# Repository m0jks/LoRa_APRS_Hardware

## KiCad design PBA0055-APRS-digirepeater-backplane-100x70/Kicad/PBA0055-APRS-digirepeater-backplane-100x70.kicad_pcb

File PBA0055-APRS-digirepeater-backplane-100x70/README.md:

This project is a Simple carrier board for a Heltec Lora WiFi V3 board.

This board can be purchased from Amazon or Aliexpress:

	https://www.aliexpress.com/item/1005007594267069.html

For LoRa APRS buy the EU433 version, for Meshtastic buy the EU868 version

The Kicad PCB in the "Kicad" directory is designed to fit in the following (120x90x70) IP67 case:

	https://www.aliexpress.com/item/1005005387771681.html

In the "Freecad" directory you will find three 3D design files.They are as follows:

1. LoRa_APRS_node_mounting_plates_100x70_studs.FCStd

This is a mounting place for the Kicad PCB inside the body of the IP67 case. It raises the PCB so that the N-Type to IPEX fitting sits neatly underneath it (and the PCB ground plane).

2. IP67_Case_38mm_mast_clamp.FCStd

This is an external mounting fixture fo the (120x90x70) case - to a 1.5" (38mm) mast. It requires two M4 nuts and bolts to clamp the two halves together.

3. IP67_Case_Antenna_Hole_Template.FCStd

This is a hole drilling template for the top N-Type and bottom SP13 power connector.

Additional Hardware.

In addition to the above PCB and 3D printed files, to complete this design you will need the following parts

1. N-Type to IPEX (U.FL) pigtail

2. SP13 Male and Female Connector

3. LM2596S Buck DC-DC board.

4. JST 1.25mm (2P) SMA

5. EU433 or EU868 Antenna

6. Heltec LoRa V3 WiFi board. EU433 for APRS, EU868 for Meshtastic

The above are all available from Aliexpress of Amazon:

1. https://www.aliexpress.com/item/1005007261632487.html
2. https://www.aliexpress.com/item/1005006769201518.html
3. https://www.aliexpress.com/item/1005006516043406.html
4. https://www.aliexpress.com/item/1005005721470475.html
5  https://www.aliexpress.com/item/1005006253283206.html
6. https://www.aliexpress.com/item/32886711232.html

Finally it is important to remember that LM2596S Buck DC-DC board has a pot top right. You need to make sure you twiddle that until the ouput (right hand side) is 5v. This is because the above PCB supplies the Heltec board with a 5v supply on pin 1

Any questions, get in touch

Dave {https://www.qrz.com/db/M0JKS)

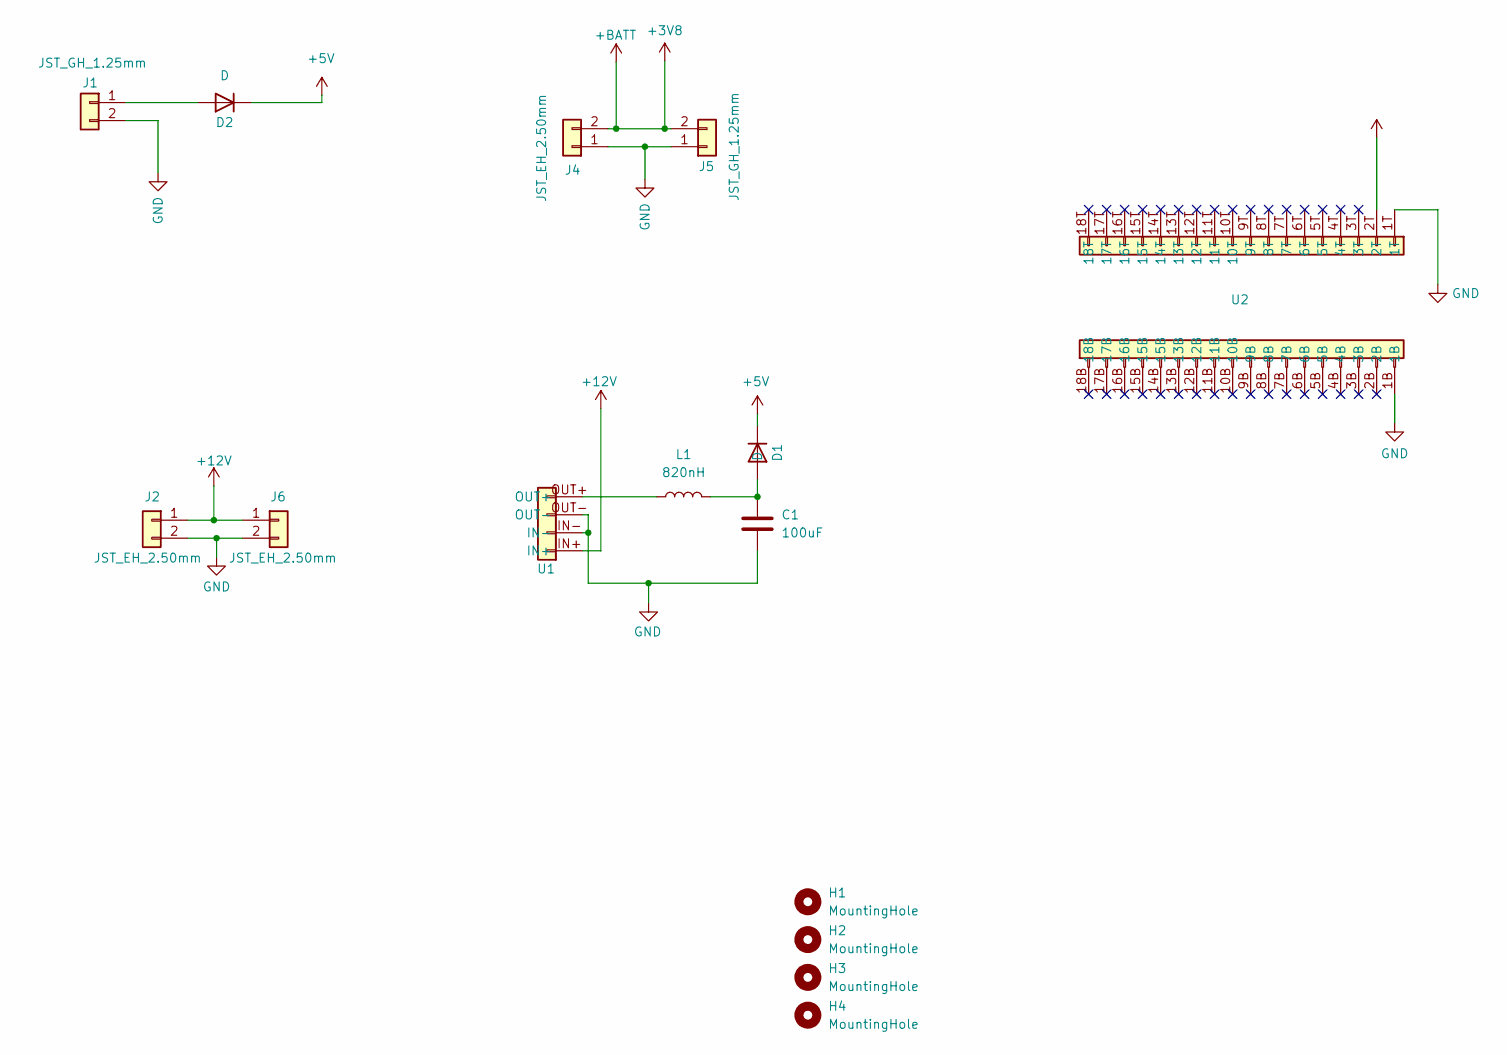
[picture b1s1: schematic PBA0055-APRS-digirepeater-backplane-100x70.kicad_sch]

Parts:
C1: 100uF; C_1210_3225Metric
D1, D2: D; D_SOD-123F
H1, H2, H3, H4: MountingHole; MountingHole_3.2mm_M3
J1: JST_GH_1.25mm; JST_PH_B2B-PH-K_1x02_P2.00mm_Vertical
J2, J4, J6: JST_EH_2.50mm; JST_EH_B2B-EH-A_1x02_P2.50mm_Vertical
J5: JST_GH_1.25mm; JST_GH_SM02B-GHS-TB_1x02-1MP_P1.25mm_Horizontal
L1: 820nH; C_1210_3225Metric
U1: LM2496_DC-DC_HW-411
U2: Heltec_LoRa_WiFi_V3_SMD

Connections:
+3V8: J4.2, J5.2
+5V: D1.1 (K), D2.1 (K), U2.2T
+12V: J2.1, J6.1, U1.IN+
GND: C1.2, J1.2, J2.2, J4.1, J5.1, J6.2, U1.IN-, U1.OUT-, U2.1B, U2.1T
unnamed: C1.1, D1.2 (A), L1.2
unnamed: D2.2 (A), J1.1
unnamed: L1.1, U1.OUT+

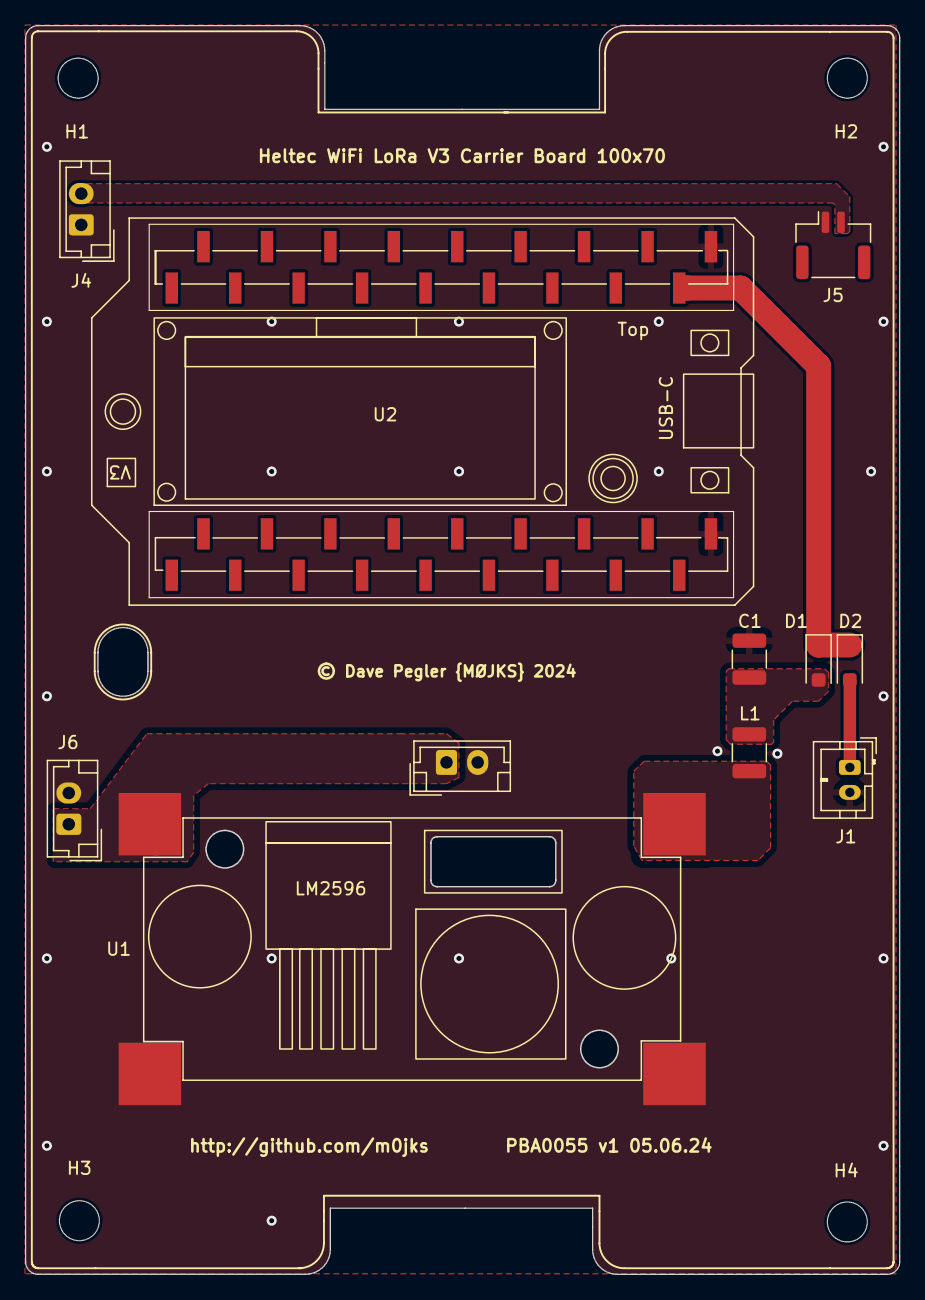
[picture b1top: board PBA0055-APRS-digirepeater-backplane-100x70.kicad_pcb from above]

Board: 2 copper layers, 70.0 x 100.0 mm, 15 parts (0 on the bottom side), 7 nets.

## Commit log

2025-01-28 PBA00055 APRS digirepeater backplane, 100x70, for IP67 case 120x90x70cm and Heltec LoRa Wifi V3 board
2025-01-28 Add PNG file of final (unstuffed) PCB
2025-01-28 Remove Gerbers
2025-01-28 Move Kicad files into Kicad directory
2025-01-28 Move all Kicad files into their own directory
2025-01-28 Mounting plate for 120x90x70mm IP67 case - available from Aliexpress
2025-01-28 Add some pictures of completed design and some BOM blurb
2025-01-28 Add 3D print designs required to complete project
2025-01-28 Some more lovely piccies
2025-01-28 Add picture or PCB from Kicad
2025-01-28 Add some piccies
2025-01-28 Add pciture of IP67 case with PBA0055 fitted
2025-01-28 Add pictures from Freecd of design files
2025-01-28 Update README with some pictures from Freecad of the brackets and mounting fixtures
2025-01-28 Incorrect file name corrected
2025-01-28 Spelling mistake
2025-03-09 Add Freecad files for type 3 (T3) APRS digirepeater case
2025-03-09 Add PCB Gerber files for type 3 (T3) APRS digirepeater case
2025-03-09 Add some photogrpahs of the type 3 (T3) APRS digirepeater (PCB and case)
2025-03-09 Add picture of PBA0058 MPPT controller PCB
2025-03-09 Add landing page
2025-03-09 Add pictures of 3D printed components
2025-03-09 Update README.md with Freecad design files
2025-03-09 Add correct BOM
2025-03-09 Add picture of Heltec Lora Wifi V3 board
2025-03-09 Remove PBA0060 screenshot
2025-03-09 Add picture of battery board
2025-03-09 Add BOM for MPPT PCB and 18650 battery board
2025-03-09 Correct incorrect reference for MPPT pcb
2025-03-09 Add reference to code
2025-03-09 Change heading to include T3 - as this a type 3

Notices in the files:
PBA0055-APRS-digirepeater-backplane-100x70/Kicad/PBA0055-APRS-digirepeater-backplane-100x70.kicad_pcb:
© Dave Pegler {MØJKS} 2024
